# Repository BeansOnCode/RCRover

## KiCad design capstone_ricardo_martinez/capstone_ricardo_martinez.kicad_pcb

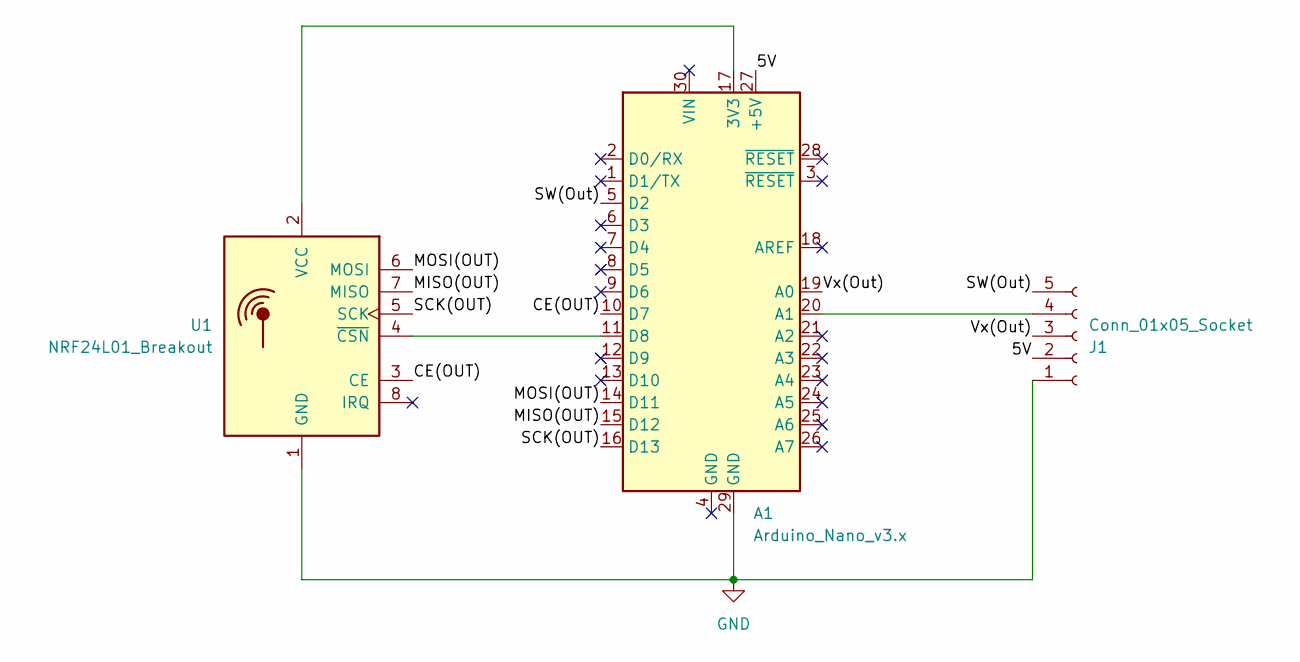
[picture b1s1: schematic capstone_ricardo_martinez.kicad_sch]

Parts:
A1: Arduino_Nano_v3.x; Arduino_Nano
J1: Conn_01x05_Socket; PinSocket_1x05_P2.54mm_Vertical
U1: NRF24L01_Breakout; nRF24L01_Breakout

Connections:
/5V: A1.27 (+5V), J1.2
/CE(OUT): A1.10 (D7), U1.3 (CE)
/MISO(OUT): A1.15 (D12), U1.7 (MISO)
/MOSI(OUT): A1.14 (D11), U1.6 (MOSI)
/SCK(OUT): A1.16 (D13), U1.5 (SCK)
/SW(Out): A1.5 (D2), J1.5
/Vx(Out): A1.19 (A0), J1.3
GND: A1.29 (GND), J1.1, U1.1 (GND)
unnamed: A1.17 (3V3), U1.2 (VCC)
unnamed: A1.20 (A1), J1.4
unnamed: A1.11 (D8), U1.4 (~CSN)

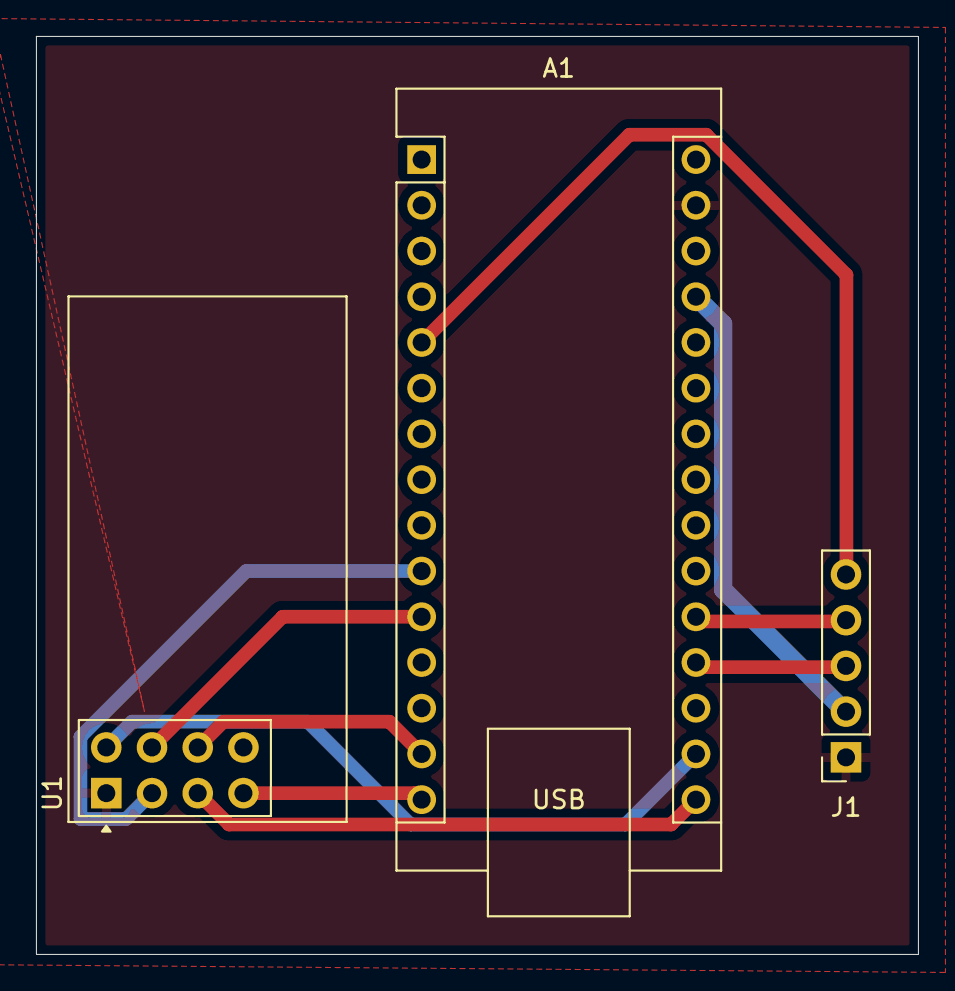
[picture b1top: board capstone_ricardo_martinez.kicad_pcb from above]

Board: 2 copper layers, 49.0 x 51.0 mm, 3 parts (0 on the bottom side), 11 nets.

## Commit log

2024-05-24 Added initial project files
2024-06-26 Added arduino sketch files and video of functioning rover
